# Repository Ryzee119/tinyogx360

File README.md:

# tinyogx360 - Overview

The tinyogx360 is a variation of my [ogx360](https://github.com/Ryzee119/ogx360) project, just a much smaller single player version. It is a circuit board which allows you to use a range of modern USB controllers on the Original Xbox Console. **Note the warnings below prior to building.**

See the main [ogx360 repo](https://github.com/Ryzee119/ogx360) for device firmware. This repo just constains the hardware design files.

This was created using [Autodesk Eagle.](https://www.autodesk.com/products/eagle/overview)

## Ordering
* The PCB Gerbers and BOM are located [here](./.kitspace/).
* These can easily be ordered via [kitspace](https://kitspace.org/boards/github.com/ryzee119/tinyogx360).
* 3D model of the PCB is [here](https://a360.co/2P1Qr6T) (Fusion360).
* You will also need to grab a  [Xbox Controller Port USB adaptor cable](https://www.aliexpress.com/wholesale?catId=0&SearchText=original+xbox+to+usb+adapter) to salvage the connector.

## Schematic

## WARNING
* Released by request. This is not as tested or as user friendly as the main ogx360 board. You should be comfortable with self-debugging.
* The board does not have any programming headers. The Atmega32u4s should come from factory with a DFU bootloader which can be programmed via the xbox side USB connector.
* I didnt have much luck with this so I hacked on a ISP programming header and programming via TinyISP or any AVR programmer.
* Alternatively program it externally.

By Ryzee119

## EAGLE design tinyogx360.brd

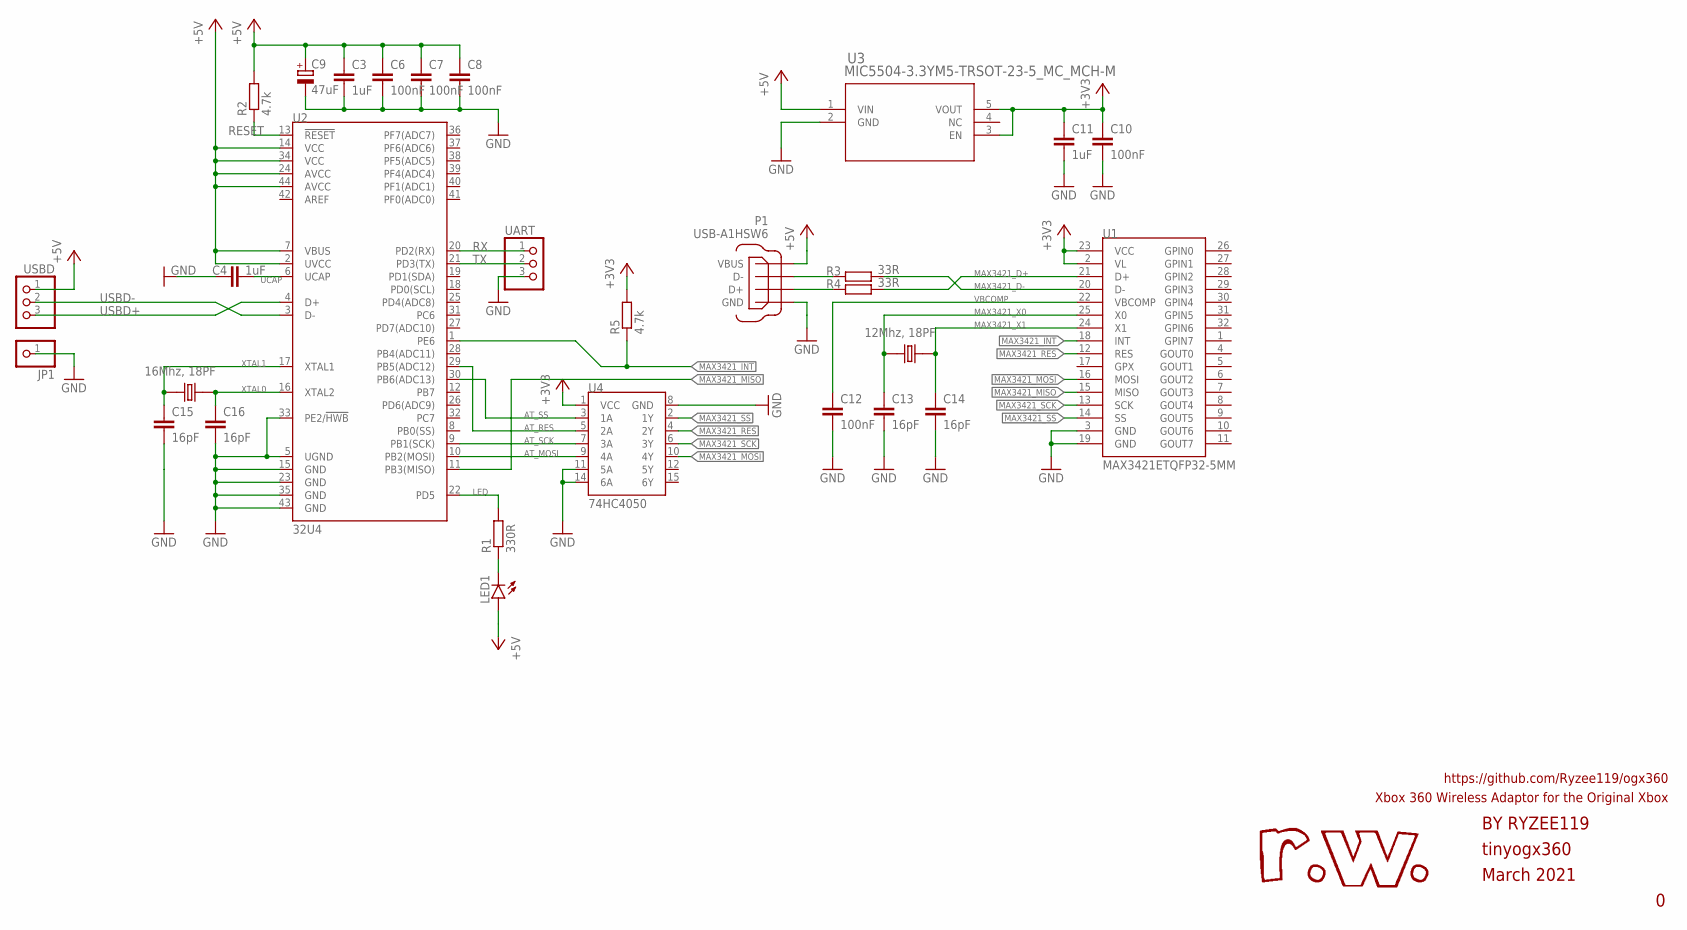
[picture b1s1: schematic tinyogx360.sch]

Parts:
C3, C4, C11: 1uF; C0805K
C6, C7, C8, C10, C12: 100nF; C0603K
C9: 47uF; 153CLV-0505
C13, C14, C15, C16: 16pF; C0603K
JP1: PINHD-1X1; 1X01
LED1: LEDCHIPLED_0603; CHIPLED_0603
P1: USB-A1HSW6; OST_USB-A1HSW6
R1: 330R; R0603
R2, R5: 4.7k; R0603
R3, R4: 33R; R0603
U1: MAX3421ETQFP32-5MM; TQFP32-5X5MM
U2: 32U4; TQFP44
U3: MIC5504-3.3YM5-TRSOT-23-5_MC_MCH-M; SOT-23-5_MC_MCH-M
U4: 74HC4050; SO16
UART: PINHD-1X3; 1X03
USBD: PINHD-1X3; 1X03
Y1: 12Mhz, 18PF; XTAL_ECS-250-18-5PX-JEM-TR
Y2: 16Mhz, 18PF; XTAL_ECS-250-18-5PX-JEM-TR

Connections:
+3V3: C10.1, C11.1, R5.2, U1.2 (VL), U1.23 (VCC), U3.3 (EN), U3.5 (VOUT), U4.1 (VCC)
+5V: C3.1, C6.1, C7.1, C8.1, C9.+, LED1.A, P1.1 (VBUS), R2.2, U2.2 (UVCC), U2.7 (VBUS), U2.14 (VCC), U2.24 (AVCC), U2.34 (VCC), U2.44 (AVCC), U3.1 (VIN), USBD.1
AT_MOSI: U2.10 (PB2(MOSI)), U4.9 (4A)
AT_RES: U2.29 (PB5(ADC12)), U4.5 (2A)
AT_SCK: U2.9 (PB1(SCK)), U4.7 (3A)
AT_SS: U2.30 (PB6(ADC13)), U4.3 (1A)
GND: C3.2, C4.1, C6.2, C7.2, C8.2, C9.-, C10.2, C11.2, C12.2, C13.2, C14.2, C15.2, C16.2, JP1.1, P1.4 (GND), U1.3 (GND), U1.19 (GND), U2.5 (UGND), U2.15 (GND), U2.23 (GND), U2.33 (PE2/!HWB), U2.35 (GND), U2.43 (GND), U3.2 (GND), U4.8 (GND), U4.11 (5A), U4.14 (6A), UART.3
LED: R1.2, U2.22 (PD5)
MAX3421_D+: R4.2, U1.21 (D+)
MAX3421_D-: R3.2, U1.20 (D-)
MAX3421_INT: R5.1, U1.18 (INT), U2.1 (PE6)
MAX3421_MISO: U1.15 (MISO), U2.11 (PB3(MISO))
MAX3421_MOSI: U1.16 (MOSI), U4.10 (4Y)
MAX3421_RES: U1.12 (RES), U4.4 (2Y)
MAX3421_SCK: U1.13 (SCK), U4.6 (3Y)
MAX3421_SS: U1.14 (SS), U4.2 (1Y)
MAX3421_X0: C13.1, U1.25 (X0), Y1.2
MAX3421_X1: C14.1, U1.24 (X1), Y1.1
unnamed: P1.2 (D-), R3.1
unnamed: P1.3 (D+), R4.1
unnamed: LED1.C, R1.1
RESET: R2.1, U2.13 (!RESET)
RX: U2.20 (PD2(RX)), UART.1
TX: U2.21 (PD3(TX)), UART.2
UCAP: C4.2, U2.6 (UCAP)
USBD+: U2.4 (D+), USBD.3
USBD-: U2.3 (D-), USBD.2
VBCOMP: C12.1, U1.22 (VBCOMP)
XTAL0: C16.1, U2.16 (XTAL2), Y2.1
XTAL1: C15.1, U2.17 (XTAL1), Y2.2

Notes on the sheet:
tinyogx360
March 2021
BY RYZEE119
Xbox 360 Wireless Adaptor for the Original Xbox
https://github.com/Ryzee119/ogx360

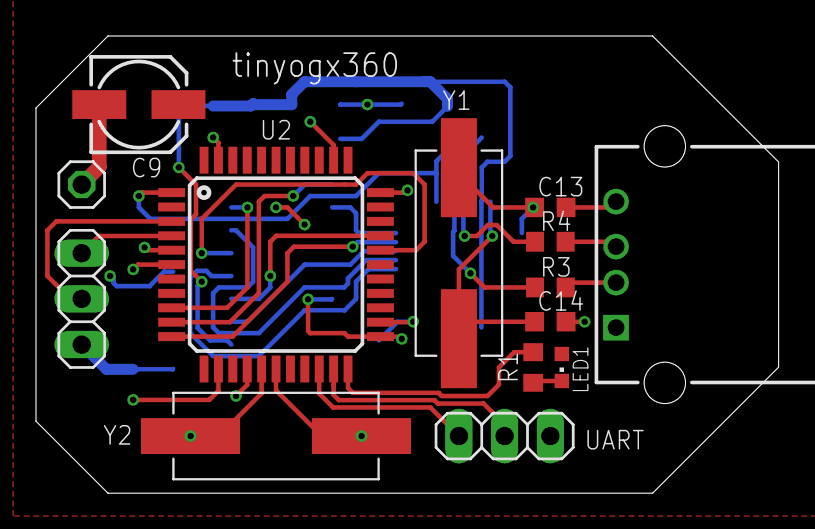
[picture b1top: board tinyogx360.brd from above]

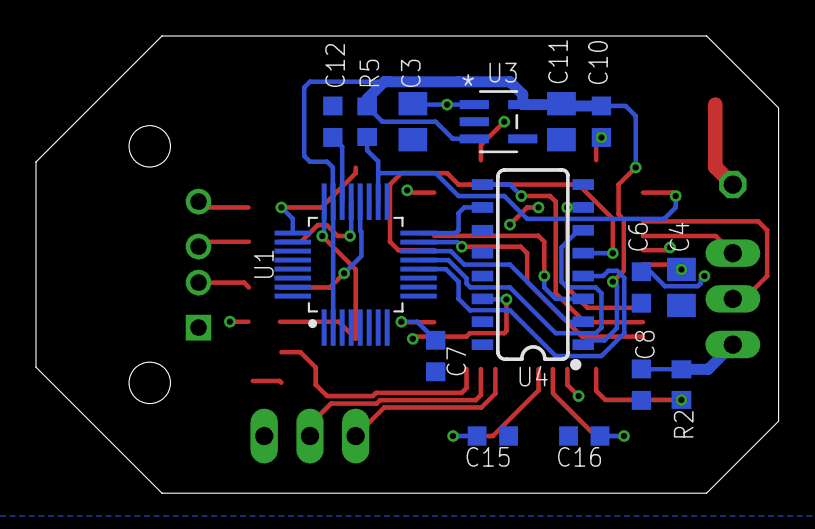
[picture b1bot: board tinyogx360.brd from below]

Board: 2 copper layers, 41.3 x 25.4 mm, 29 parts (15 on the bottom side), 30 nets.

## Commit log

2021-03-18 Fix kitspace bom.csv formatting
2021-03-18 Readme: Additional warning text added
2021-03-18 Readme: Link to firmware added

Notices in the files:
parts and their libraries:
SparkFun-IC-Microcontroller: Licensing: Creative Commons ShareAlike 4.0 International - https://creativecommons.org/licenses/by-sa/4.0
COPYRIGHT: Copyright (C) 2018 Accelerated Designs. All rights reserved
